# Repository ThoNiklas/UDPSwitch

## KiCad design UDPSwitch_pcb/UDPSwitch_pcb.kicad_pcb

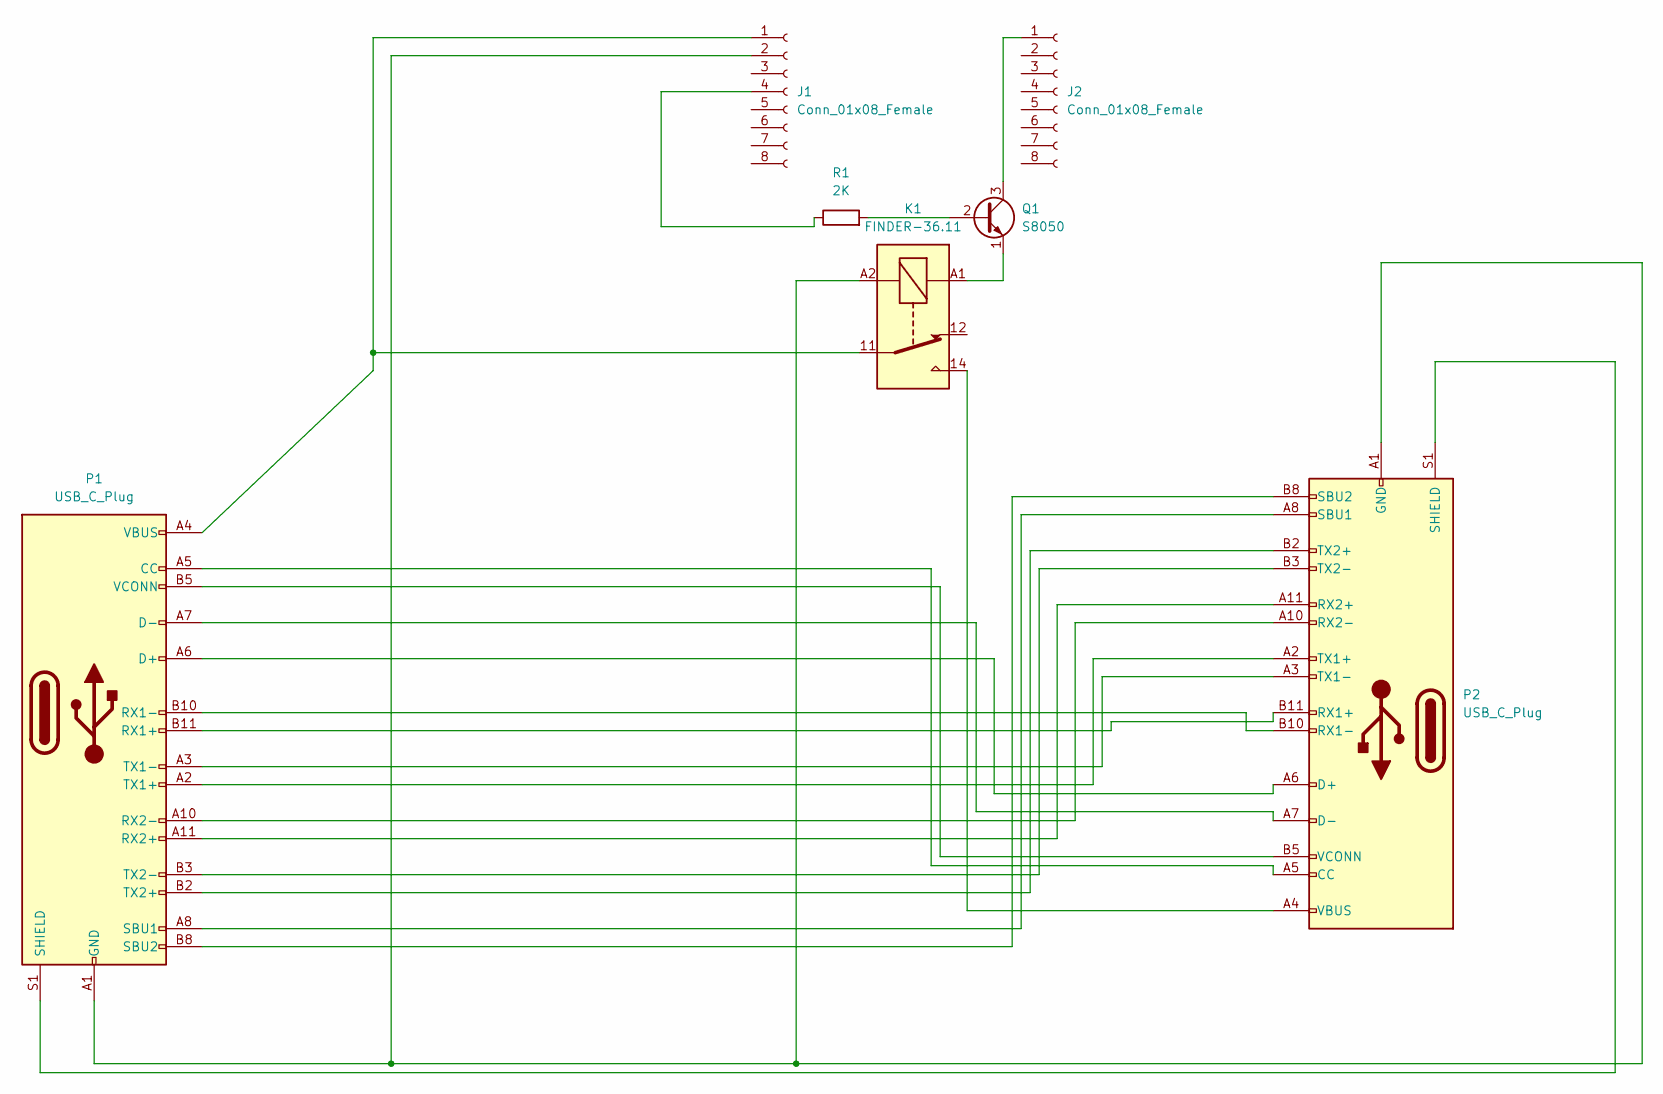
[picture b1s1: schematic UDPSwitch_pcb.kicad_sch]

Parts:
J1, J2: Conn_01x08_Female; PinSocket_1x08_P2.54mm_Vertical
K1: FINDER-36.11; Relay_SPDT_Finder_36.11
P1, P2: USB_C_Plug; USB_C_Plug_Molex_105444
Q1: S8050; TO-92_Inline
R1: 2K; R_0805_2012Metric

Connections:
unnamed: J1.1, K1.11, P1.A4 (VBUS), P1.A9 (VBUS), P1.B4 (VBUS), P1.B9 (VBUS)
unnamed: J1.2, K1.A2, P1.A1 (GND), P1.A12 (GND), P1.B1 (GND), P1.B12 (GND), P2.A1 (GND), P2.A12 (GND), P2.B1 (GND), P2.B12 (GND)
unnamed: J1.4, R1.1
unnamed: J2.1, Q1.3 (C)
unnamed: K1.14, P2.A4 (VBUS), P2.A9 (VBUS), P2.B4 (VBUS), P2.B9 (VBUS)
unnamed: K1.A1, Q1.1 (E)
unnamed: P1.A2 (TX1+), P2.A2 (TX1+)
unnamed: P1.A3 (TX1-), P2.A3 (TX1-)
unnamed: P1.A5 (CC), P2.A5 (CC)
unnamed: P1.A6 (D+), P2.A6 (D+)
unnamed: P1.A7 (D-), P2.A7 (D-)
unnamed: P1.A8 (SBU1), P2.A8 (SBU1)
unnamed: P1.A10 (RX2-), P2.A10 (RX2-)
unnamed: P1.A11 (RX2+), P2.A11 (RX2+)
unnamed: P1.B2 (TX2+), P2.B2 (TX2+)
unnamed: P1.B3 (TX2-), P2.B3 (TX2-)
unnamed: P1.B5 (VCONN), P2.B5 (VCONN)
unnamed: P1.B8 (SBU2), P2.B8 (SBU2)
unnamed: P1.B10 (RX1-), P2.B10 (RX1-)
unnamed: P1.B11 (RX1+), P2.B11 (RX1+)
unnamed: P1.S1 (SHIELD), P2.S1 (SHIELD)
unnamed: Q1.2 (B), R1.2

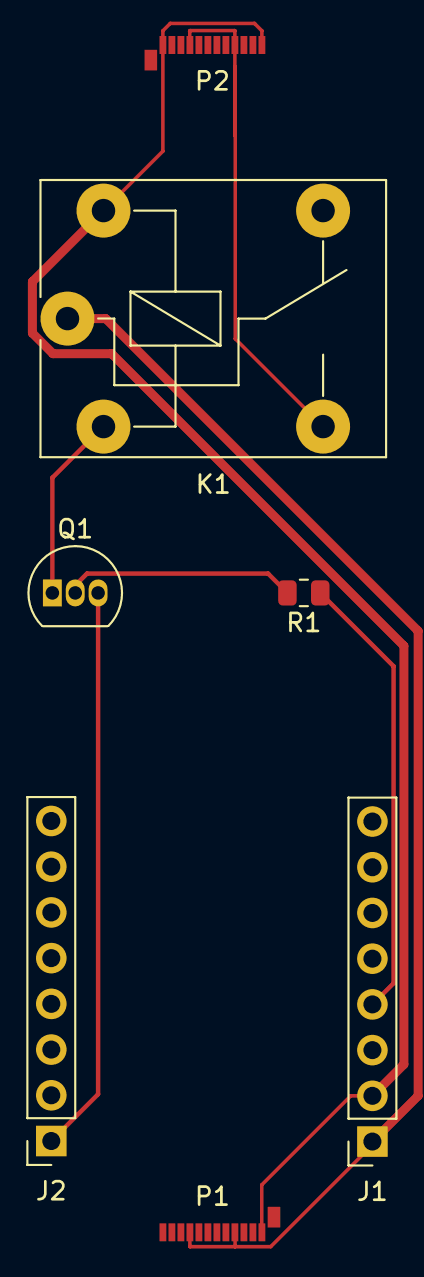
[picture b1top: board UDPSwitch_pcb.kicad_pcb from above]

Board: 2 copper layers, 7 parts (0 on the bottom side), 22 nets.

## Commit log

2023-01-14 first version of the PCB (not finished)
